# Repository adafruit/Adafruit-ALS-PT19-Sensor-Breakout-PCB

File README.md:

## Adafruit ALS-PT19 Analog Light Sensor Breakout PCB
<a href="http://www.adafruit.com/products/2748"><br/>
Click here to purchase one from the Adafruit shop</a>

Add a teeny analog light sensor, the ALS PT19 analog light sensor is a great way to upgrade a project that uses a photocell and needs RoHS compliance. Due to the high rejection ratio of infrared radiation, the spectral response of the ambient light sensor is close to that of human eyes.

PCB files for the Adafruit ALS-PT19 Sensor Breakout. The format is EagleCAD schematic and board layout
- https://www.adafruit.com/product/2748

### License

Adafruit invests time and resources providing this open source design, please support Adafruit and open-source hardware by purchasing products from [Adafruit](https://www.adafruit.com)!

All text above must be included in any redistribution

Designed by Limor Fried/Ladyada for Adafruit Industries.
Creative Commons Attribution/Share-Alike, all text above must be included in any redistribution. 
See license.txt for additional information.

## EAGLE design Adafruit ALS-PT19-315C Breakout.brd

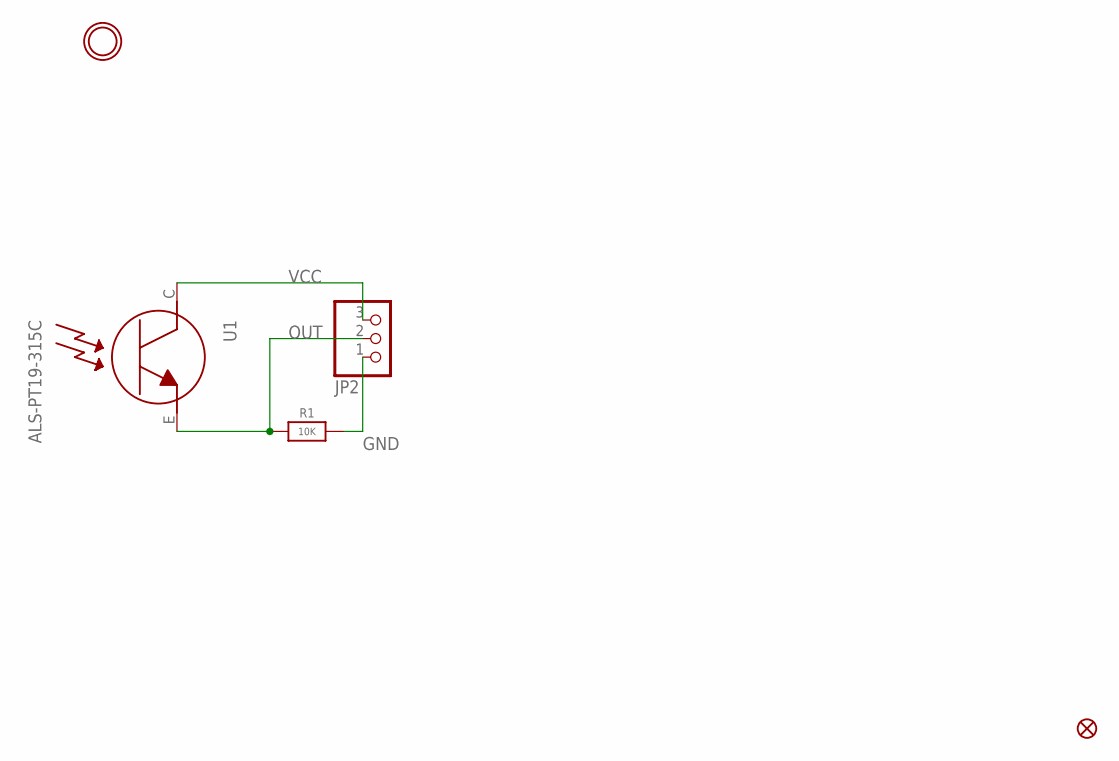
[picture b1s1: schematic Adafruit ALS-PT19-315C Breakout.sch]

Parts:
FID1: FIDUCIAL""; FIDUCIAL_1MM
JP2: HEADER-1X3ROUND; 1X03_ROUND
R1: 10K; 0603-NO
U1: ALS-PT19-315C
U$2: MOUNTINGHOLE2.0; MOUNTINGHOLE_2.0_PLATED

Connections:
GND: JP2.1, R1.1
OUT: JP2.2, R1.2, U1.E
VCC: JP2.3, U1.C

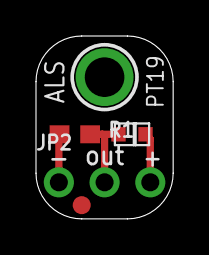
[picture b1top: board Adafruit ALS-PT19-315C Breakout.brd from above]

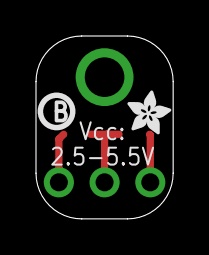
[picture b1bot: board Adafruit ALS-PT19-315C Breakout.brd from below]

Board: 2 copper layers, 7.6 x 10.2 mm, 7 parts (2 on the bottom side), 3 nets.

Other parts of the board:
U$1: ADAFRUIT_2.5MM
U$3: PCBFEAT-REV-040

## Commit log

2016-06-24 files!

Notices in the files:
parts and their libraries:
microbuilder: This work is placed in the public domain, and may be freely used for commercial and non-commercial work with the following conditions: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
